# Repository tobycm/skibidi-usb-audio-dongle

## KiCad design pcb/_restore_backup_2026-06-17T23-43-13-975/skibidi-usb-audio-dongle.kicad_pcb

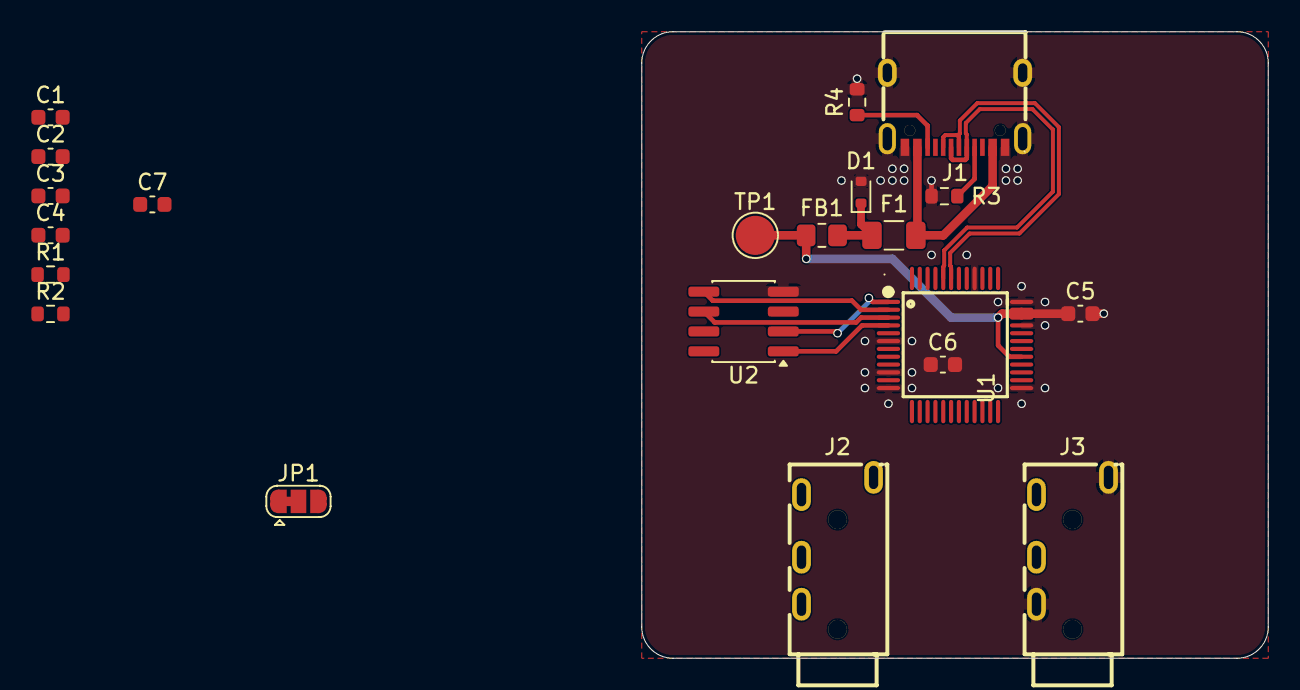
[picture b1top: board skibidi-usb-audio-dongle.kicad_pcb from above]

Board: 2 copper layers, 40.0 x 40.0 mm, 21 parts (0 on the bottom side), 22 nets.

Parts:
C1, C2, C3, C4, C5, C6: 2.2u; C_0603_1608Metric
C7: 100n; C_0603_1608Metric
D1: 5V; D_SOD-523
F1: 2A; Fuse_1206_3216Metric
FB1: 220Ω@100MHz; R_0805_2012Metric_Pad1.20x1.40mm_HandSolder
J1: USB_C_Receptacle_USB2.0_16P; USB-C-SMD_TYPE-C-16PIN-2MD-073
J2: Headphones; AUDIO-TH_PJ-320A-4P-DIP
J3: Mic; AUDIO-TH_PJ-320A-4P-DIP
JP1: SolderJumper_3_Bridged12; SolderJumper-3_P1.3mm_Bridged12_RoundedPad1.0x1.5mm
R1: 2.7k; R_0603_1608Metric
R2: 1k; R_0603_1608Metric
R3, R4: 5.1k; R_0603_1608Metric
TP1: TestPoint; TestPoint_Pad_D2.5mm
U1: HS-100B; LQFP-48_L7.0-W7.0-P0.50-LS9.0-BL
U2: 25Q4; SOP-8_3.76x4.96mm_P1.27mm

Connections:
+3V3: C6.1, C7.1, U1.8 (DREG33), U2.8 (VCC)
+5V: C5.1, FB1.2, TP1.1 (1_1), U1.29 (AVDD), U1.34 (AVDD), U1.35 (DVDD)
/CS: U1.4 (CS), U2.1 (~CS)
/D+: J1.A6 (D+), J1.B6 (D+), U1.43 (USBDP)
/D-: J1.A7 (D-), J1.B7 (D-), U1.44 (USBDM)
/MISO: U1.1 (DR), U2.2 (DO/IO_{1})
/MOSI: U1.2 (DW), U2.5 (DI/IO_{0})
/SCK: U1.3 (SK), U2.6 (CLK)
GND: C1.2, C2.2, C3.2, C4.2, C5.2, C6.2, C7.2, D1.2 (A2), J1.A1 (GND), J1.B1 (GND), J1.SH (SHIELD), J3.R2, J3.S, JP1.3 (B), R3.2, R4.2, U1.6 (PWRSEL), U1.10 (MODE), U1.12 (DVSS), U1.25 (AVSS), U1.33 (AVSS), U1.36 (DVSS), U1.40 (MSEL), U2.4 (GND)
unnamed: C3.1, C4.1, R1.2, R2.1
unnamed: D1.1 (A1), F1.2, FB1.1
unnamed: F1.1, J1.A4 (VBUS), J1.B4 (VBUS)
unnamed: J1.A5 (CC1), R3.1
unnamed: J1.B5 (CC2), R4.1
unnamed: J3.R1, R2.2
unnamed: JP1.1 (A), U1.31 (LOBS)
unnamed: J2.R2, J2.S, JP1.2 (C)
unnamed: J2.T, U1.30 (LOL)
unnamed: J2.R1, U1.32 (LOR)
unnamed: J3.T, U1.28 (MICIN)
unnamed: R1.1, U1.26 (VBIAS)
unnamed: C1.1, C2.1, U1.27 (VREF)
